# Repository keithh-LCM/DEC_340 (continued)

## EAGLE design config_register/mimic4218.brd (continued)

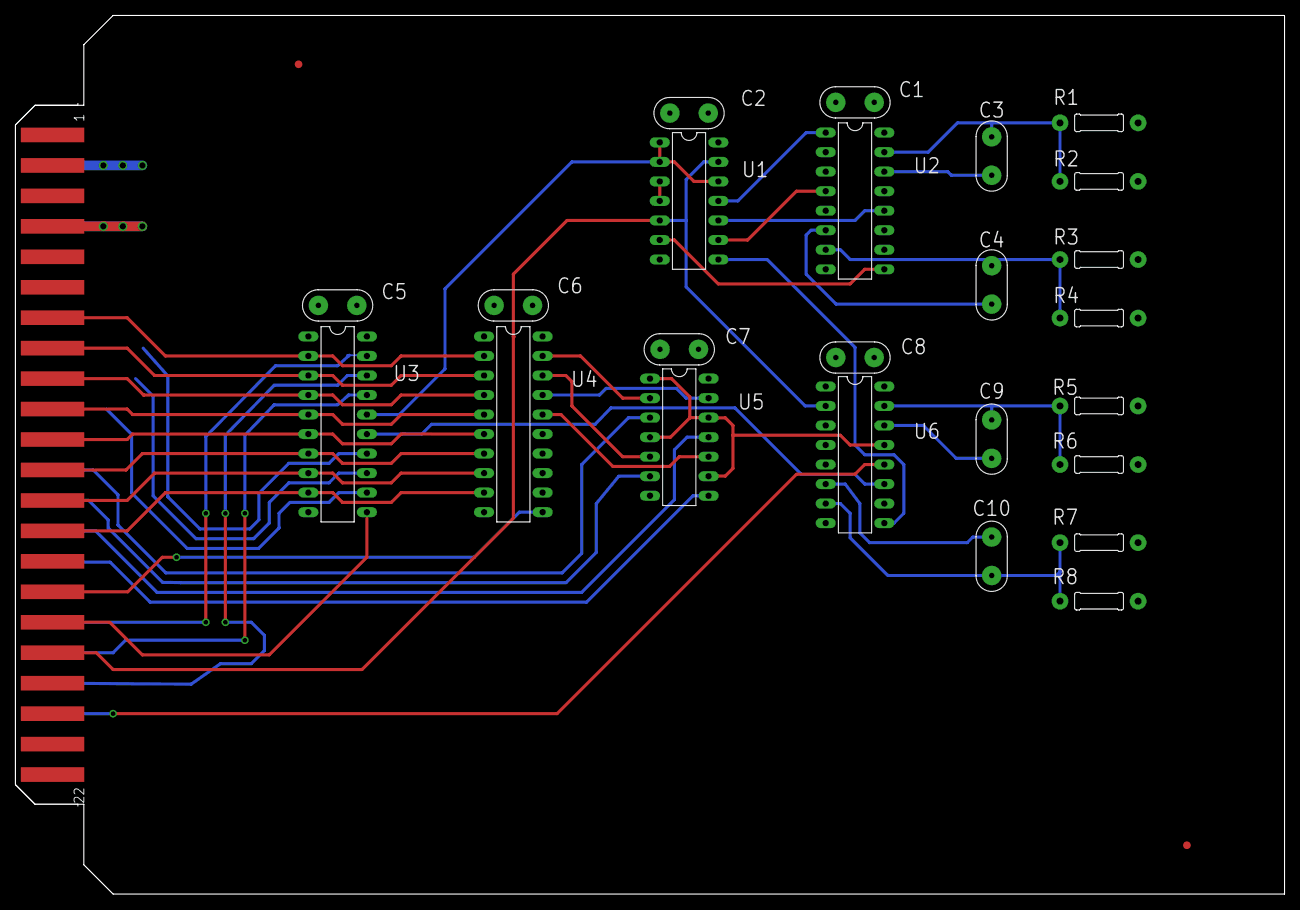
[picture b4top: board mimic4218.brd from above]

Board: 4 copper layers, 165.1 x 114.3 mm, 27 parts (0 on the bottom side), 42 nets.

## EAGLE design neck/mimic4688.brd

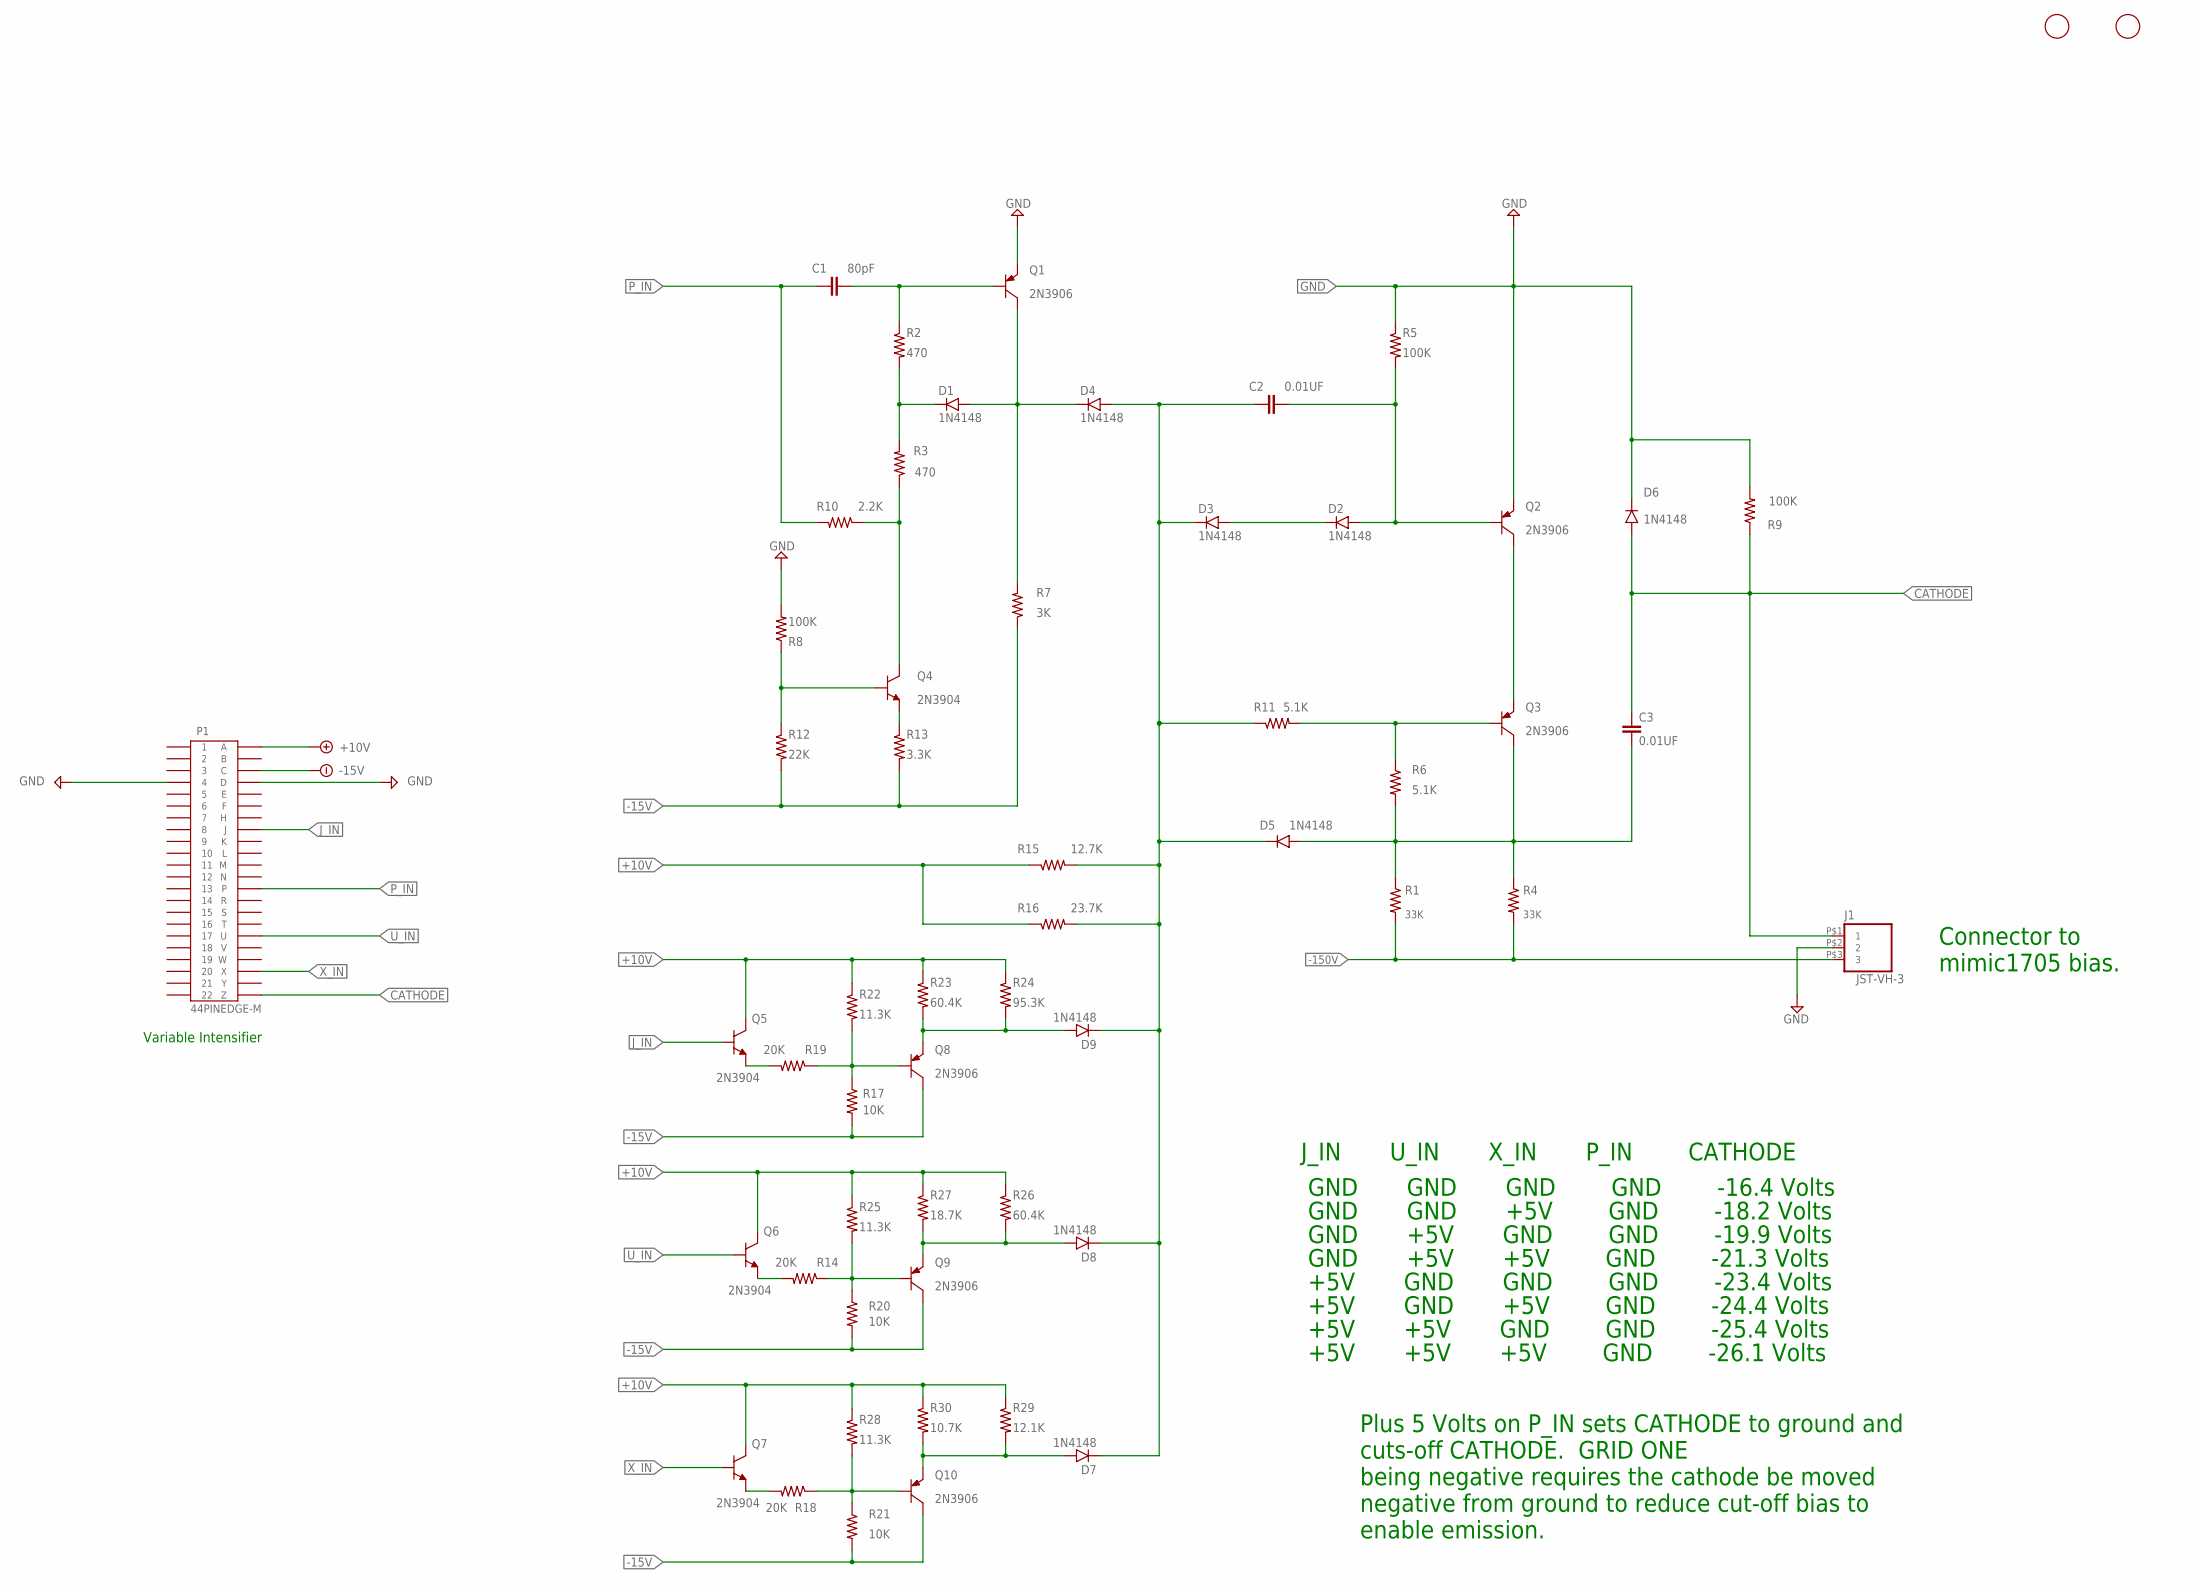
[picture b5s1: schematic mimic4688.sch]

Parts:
C1: 80pF; 5MM_TH
C2, C3: 0.01UF; 5MM_TH
D1, D2, D3, D4, D5, D6, D7, D8, D9: 1N4148; DO35-7
J1: JST-VH-3; VHR-3N
P1: 44PINEDGE-M; 44PINEDGE
Q1, Q2, Q3, Q8, Q9, Q10: 2N3906; TO92
Q4, Q5, Q6, Q7: 2N3904; TO92
R1, R4: 33K; RR02
R2, R3: 470; 0207/10
R5, R8, R9: 100K; 0207/10
R6, R11: 5.1K; 0207/10
R7: 3K; 0207/10
R10: 2.2K; 0207/10
R12: 22K; 0207/10
R13: 3.3K; 0207/10
R14, R18, R19: 20K; 0207/10
R15: 12.7K; 0207/10
R16: 23.7K; 0207/10
R17, R20, R21: 10K; 0207/10
R22, R25, R28: 11.3K; 0207/10
R23, R26: 60.4K; 0207/10
R24: 95.3K; 0207/10
R27: 18.7K; 0207/10
R29: 12.1K; 0207/10
R30: 10.7K; 0207/10
U$1, U$2: FIDUCIAL; FIDUCIAL_1MM

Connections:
+10V: P1.A, Q5.3 (C), Q6.3 (C), Q7.3 (C), R15.1, R16.1, R22.1, R23.1, R24.1, R25.1, R26.1, R27.1, R28.1, R29.1, R30.1
-15V: P1.C, Q8.1 (C), Q9.1 (C), Q10.1 (C), R7.1, R12.2, R13.2, R17.2, R20.2, R21.2
-150V: J1.P$3 (3), R1.2, R4.2
CATHODE: C3.1, D6.A, J1.P$1 (1), P1.Z, R9.1
GND: D6.C, J1.P$2 (2), P1.4, P1.D, Q1.3 (E), Q2.3 (E), R5.1, R8.2, R9.2
J_IN: P1.J, Q5.2 (B)
unnamed: C1.2, Q1.2 (B), R2.1
unnamed: Q9.2 (B), R14.1, R20.1, R25.2
unnamed: D8.A, Q9.3 (E), R26.2, R27.2
unnamed: Q7.1 (E), R18.2
unnamed: Q10.2 (B), R18.1, R21.1, R28.2
unnamed: Q6.1 (E), R14.2
unnamed: D1.A, D4.C, Q1.1 (C), R7.2
unnamed: D1.C, R2.2, R3.2
unnamed: Q4.3 (C), R3.1, R10.1
unnamed: Q5.1 (E), R19.2
unnamed: Q4.1 (E), R13.1
unnamed: Q4.2 (B), R8.1, R12.1
unnamed: Q8.2 (B), R17.1, R19.1, R22.2
unnamed: D2.C, D3.A
unnamed: Q2.1 (C), Q3.3 (E)
unnamed: D9.A, Q8.3 (E), R23.2, R24.2
unnamed: D7.A, Q10.3 (E), R29.2, R30.2
unnamed: Q3.2 (B), R6.1, R11.2
unnamed: C2.2, D2.A, Q2.2 (B), R5.2
unnamed: C2.1, D3.C, D4.A, D5.C, D7.C, D8.C, D9.C, R11.1, R15.2, R16.2
P_IN: C1.1, P1.P, R10.2
U_IN: P1.U, Q6.2 (B)
X_IN: P1.X, Q7.2 (B)
Y_OUT: C3.2, D5.A, Q3.1 (C), R1.1, R4.1, R6.2

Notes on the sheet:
Plus 5 Volts on P_IN sets CATHODE to ground and cuts-off CATHODE. GRID ONE being negative requires the cathode be moved negative from ground to reduce cut-off bias to enable emission.
J_IN U_IN X_IN P_IN CATHODE
GND GND GND GND -16.4 Volts
GND GND +5V GND -18.2 Volts
GND +5V GND GND -19.9 Volts
GND +5V +5V GND -21.3 Volts
+5V GND GND GND -23.4 Volts
+5V GND +5V GND -24.4 Volts
+5V +5V GND GND -25.4 Volts
+5V +5V +5V GND -26.1 Volts
Connector to mimic1705 bias.
Variable Intensifier

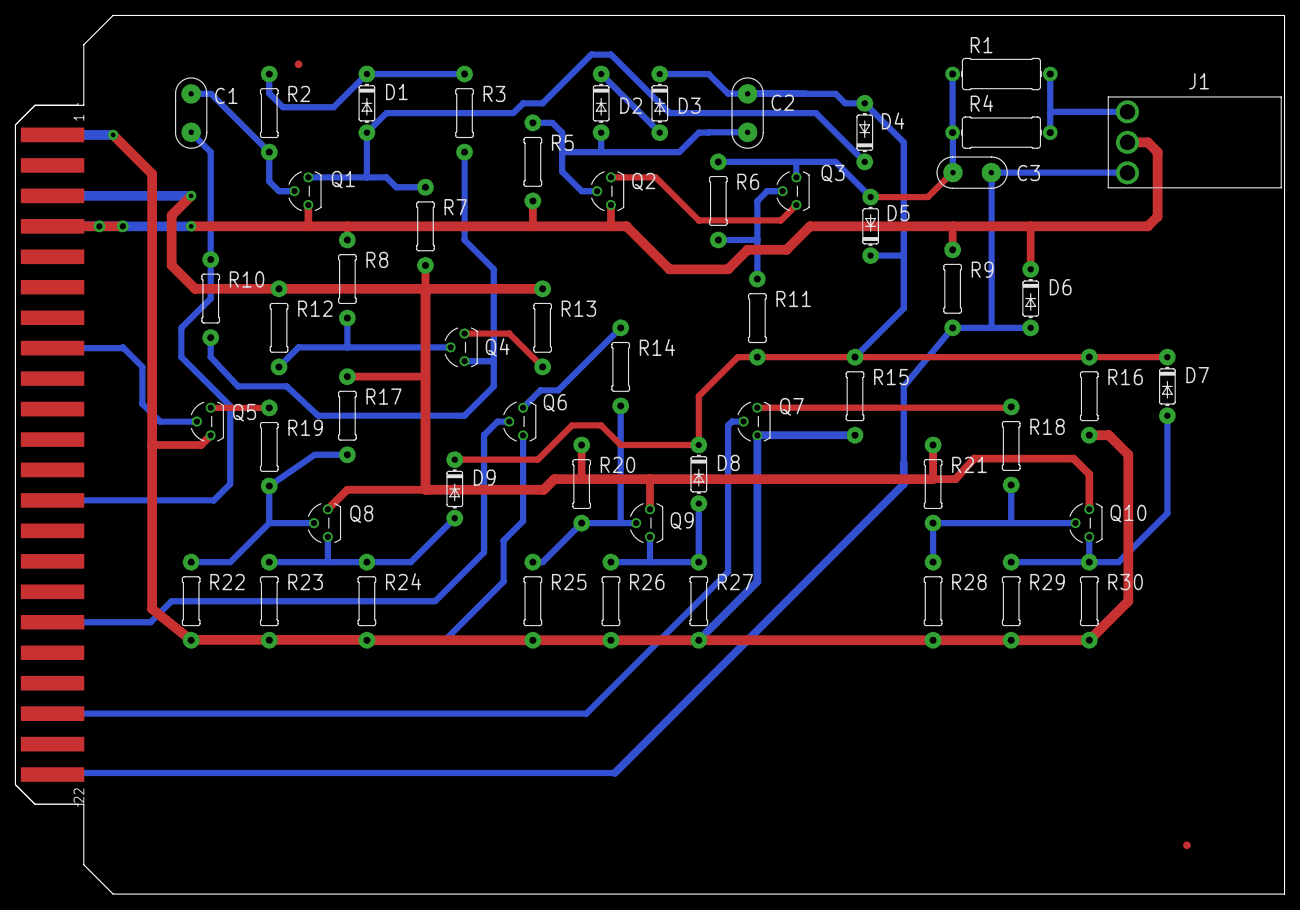
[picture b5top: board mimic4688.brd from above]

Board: 2 copper layers, 165.1 x 114.3 mm, 56 parts (0 on the bottom side), 30 nets.

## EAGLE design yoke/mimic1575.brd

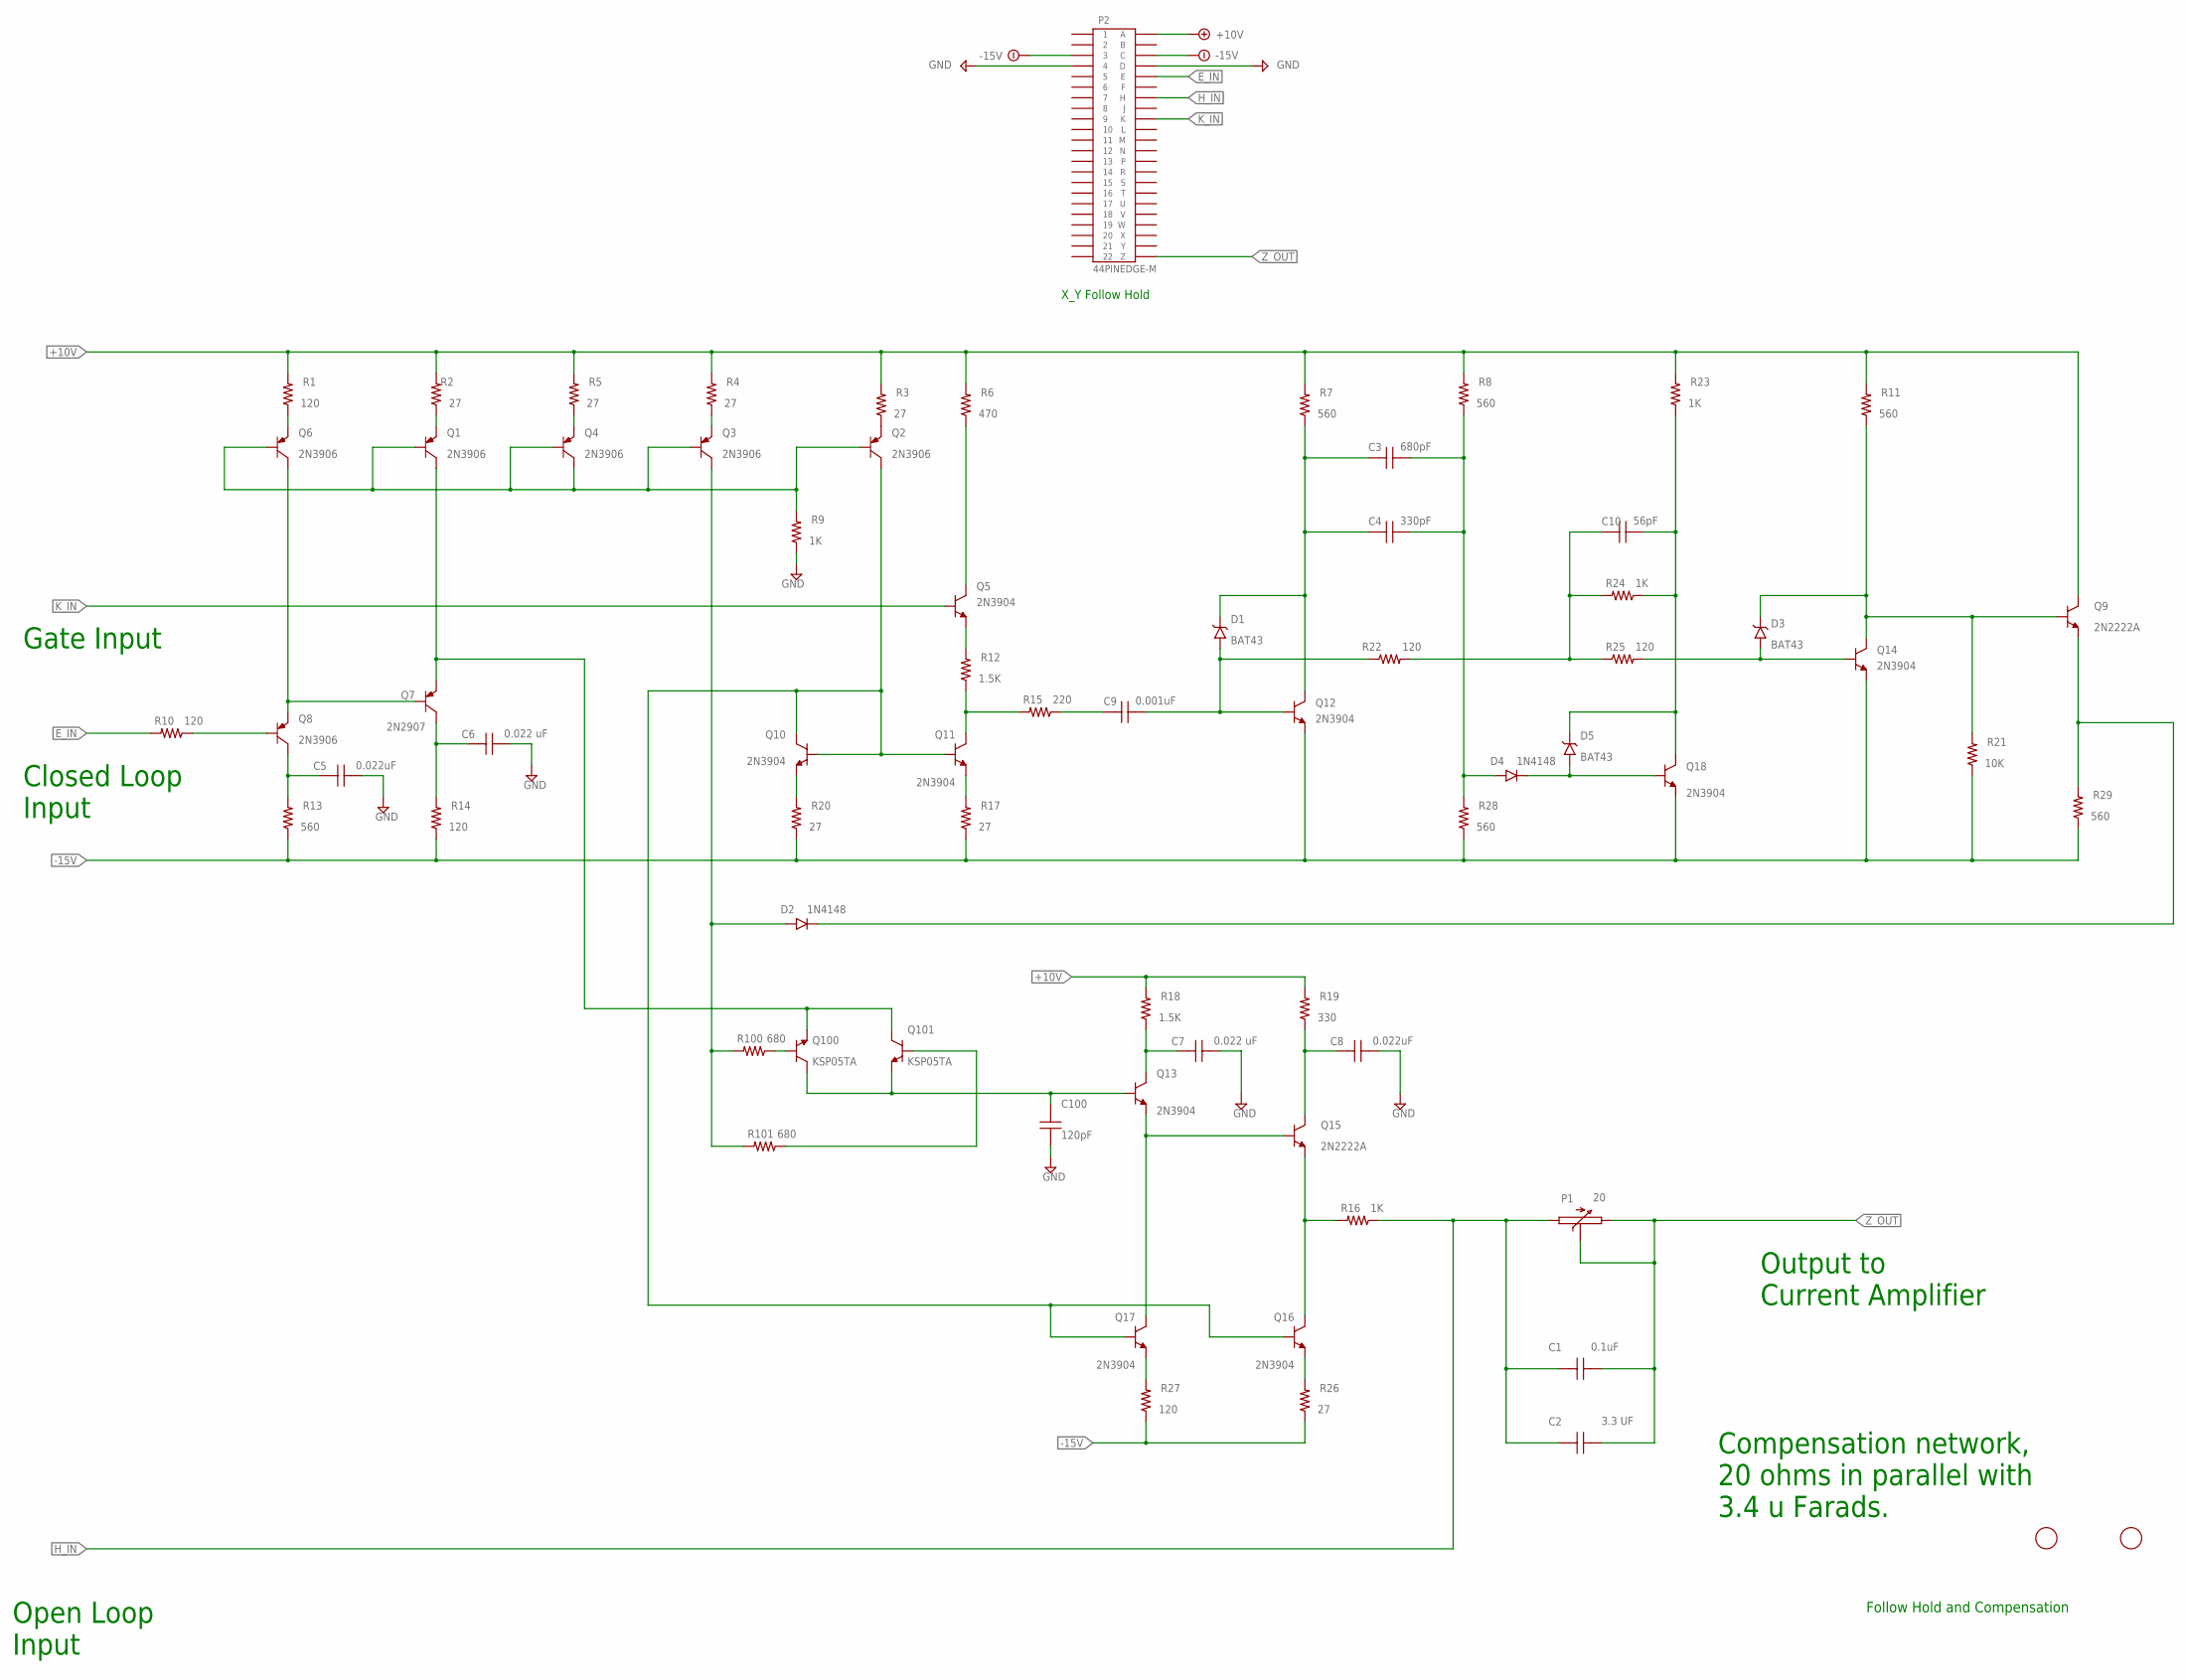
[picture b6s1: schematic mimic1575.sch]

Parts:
C1: 0.1uF; 5MM_TH
C2: 3.3 UF; ECW-FD2W335K
C3: 680pF; 5MM_TH; MPN 1000 pf
C4: 330pF; 5MM_TH; MPN 1000 pf
C5, C8: 0.022uF; CAP-ZERO-PT-ZERO-22UF-250V-FILM
C6, C7: 0.022 uF; CAP-ZERO-PT-ZERO-22UF-250V-FILM
C9: 0.001uF; 5MM_TH; MPN 1000 pf
C10: 56pF; 5MM_TH; MPN 68 pF
C100: 120pF; 5MM_TH; MPN 1000 pf
D1, D3, D5: BAT43; DO35-7
D2, D4: 1N4148; DO35-7
P1: 20; 3006P
P2: 44PINEDGE-M; 44PINEDGE
Q1, Q2, Q3, Q4, Q6, Q8: 2N3906; TO92
Q5, Q10, Q11, Q12, Q13, Q14, Q16, Q17, Q18: 2N3904; TO92
Q7: 2N2907; TO18
Q9, Q15: 2N2222A; TO18
Q100, Q101: KSP05TA; TO92
R1, R10, R14, R22, R25, R27: 120; R_QUARTERWATT
R2, R3, R4, R5, R17, R20, R26: 27; R_QUARTERWATT
R6: 470; R_QUARTERWATT
R7, R8, R11, R13, R28, R29: 560; R_QUARTERWATT
R9, R16, R23, R24: 1K; R_QUARTERWATT
R12, R18: 1.5K; R_QUARTERWATT
R15: 220; R_QUARTERWATT
R19: 330; R_QUARTERWATT
R21: 10K; R_QUARTERWATT
R100, R101: 680; R_QUARTERWATT
U$1, U$2: FIDUCIAL; FIDUCIAL_1MM

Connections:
+10V: P2.A, Q9.3 (C), R1.2, R2.2, R3.2, R4.2, R5.2, R6.2, R7.2, R8.2, R11.2, R18.2, R19.2, R23.2
-15V: P2.3, P2.C, Q12.1 (E), Q14.1 (E), Q18.1 (E), R13.1, R14.1, R17.1, R20.1, R21.1, R26.1, R27.1, R28.1, R29.1
E_IN: P2.E, R10.2
GND: C5.1, C6.1, C7.1, C8.1, C100.2, P2.4, P2.D, R9.1
H_IN: C1.1, C2.1, P1.1, P2.H, R16.1
K_IN: P2.K, Q5.2 (B)
unnamed: C9.1, R15.1
unnamed: C3.1, C4.1, D1.C, Q12.3 (C), R7.1
unnamed: C9.2, D1.A, Q12.2 (B), R22.1
unnamed: C10.1, R22.2, R24.2, R25.1
unnamed: C10.2, D5.C, Q18.3 (C), R23.1, R24.1
unnamed: D2.C, Q9.1 (E), R29.2
unnamed: Q10.1 (E), R20.2
unnamed: D4.C, D5.A, Q18.2 (B)
unnamed: C3.2, C4.2, D4.A, R8.1, R28.2
unnamed: Q4.3 (E), R5.1
unnamed: D3.C, Q9.2 (B), Q14.3 (C), R11.1, R21.2
unnamed: D3.A, Q14.2 (B), R25.2
unnamed: C6.2, Q7.3 (C), R14.2
unnamed: Q2.1 (C), Q10.2 (B), Q10.3 (C), Q11.2 (B), Q16.2 (B), Q17.2 (B)
unnamed: Q1.1 (C), Q7.1 (E), Q100.1 (E), Q101.3 (C)
unnamed: Q3.3 (E), R4.1
unnamed: Q100.2 (B), R100.1
unnamed: Q17.1 (E), R27.2
unnamed: Q101.2 (B), R101.1
unnamed: C100.1, Q13.2 (B), Q100.3 (C), Q101.1 (E)
unnamed: Q1.2 (B), Q2.2 (B), Q3.2 (B), Q4.1 (C), Q4.2 (B), Q6.2 (B), R9.2
unnamed: Q13.1 (E), Q15.2 (B), Q17.3 (C)
unnamed: D2.A, Q3.1 (C), R100.2, R101.2
unnamed: Q2.3 (E), R3.1
unnamed: Q8.2 (B), R10.1
unnamed: Q6.3 (E), R1.1
unnamed: C7.2, Q13.3 (C), R18.1
unnamed: Q11.1 (E), R17.2
unnamed: Q6.1 (C), Q7.2 (B), Q8.3 (E)
unnamed: C5.2, Q8.1 (C), R13.2
unnamed: Q1.3 (E), R2.1
unnamed: Q11.3 (C), R12.1, R15.2
unnamed: Q16.1 (E), R26.2
unnamed: Q5.1 (E), R12.2
unnamed: Q5.3 (C), R6.1
unnamed: Q15.1 (E), Q16.3 (C), R16.2
unnamed: C8.2, Q15.3 (C), R19.1
Z_OUT: C1.2, C2.2, P1.2, P1.3, P2.Z

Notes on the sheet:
Follow Hold and Compensation
Compensation network, 20 ohms in parallel with 3.4 u Farads.
Open Loop Input
Closed Loop Input
Gate Input
Output to Current Amplifier
X_Y Follow Hold

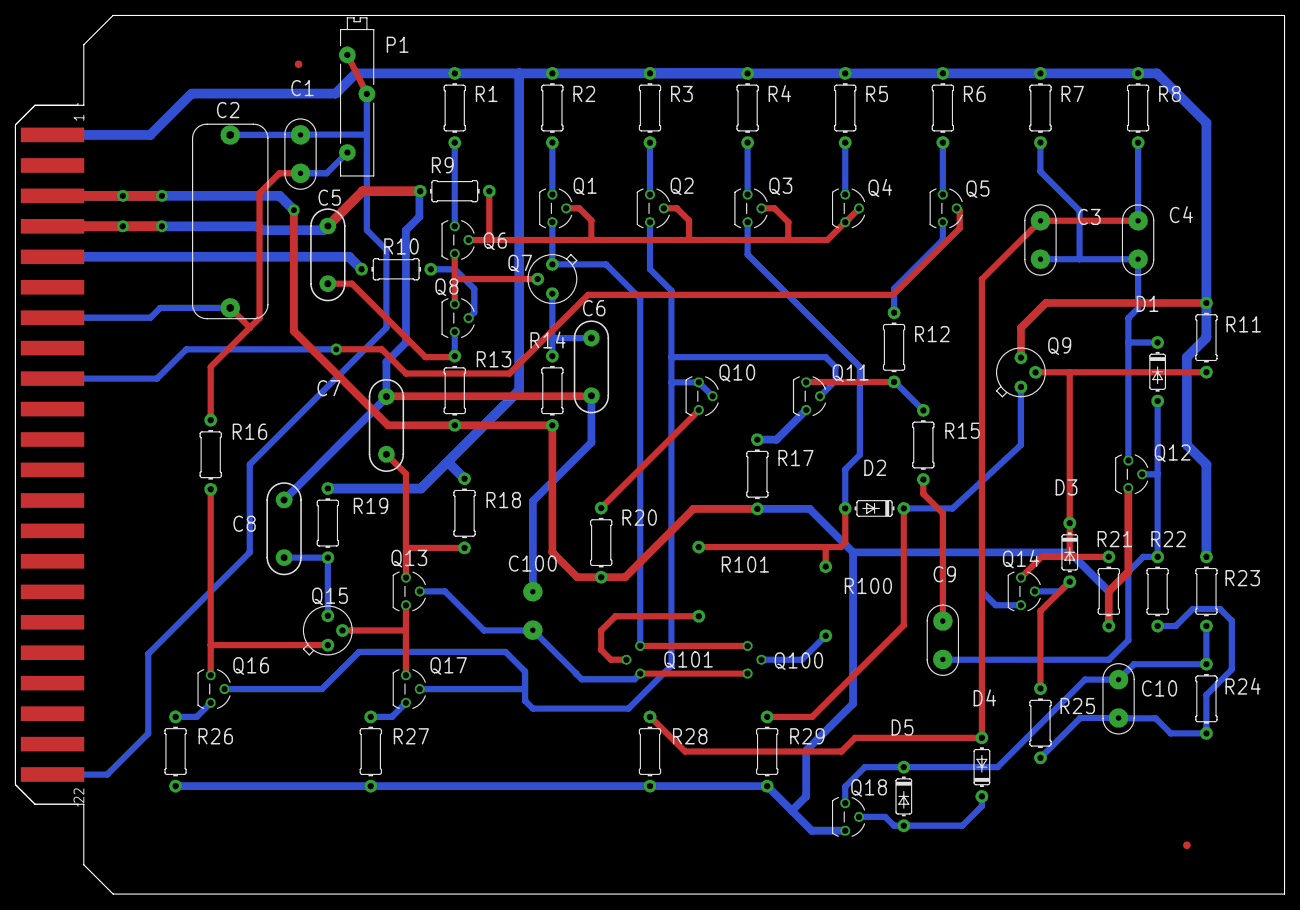
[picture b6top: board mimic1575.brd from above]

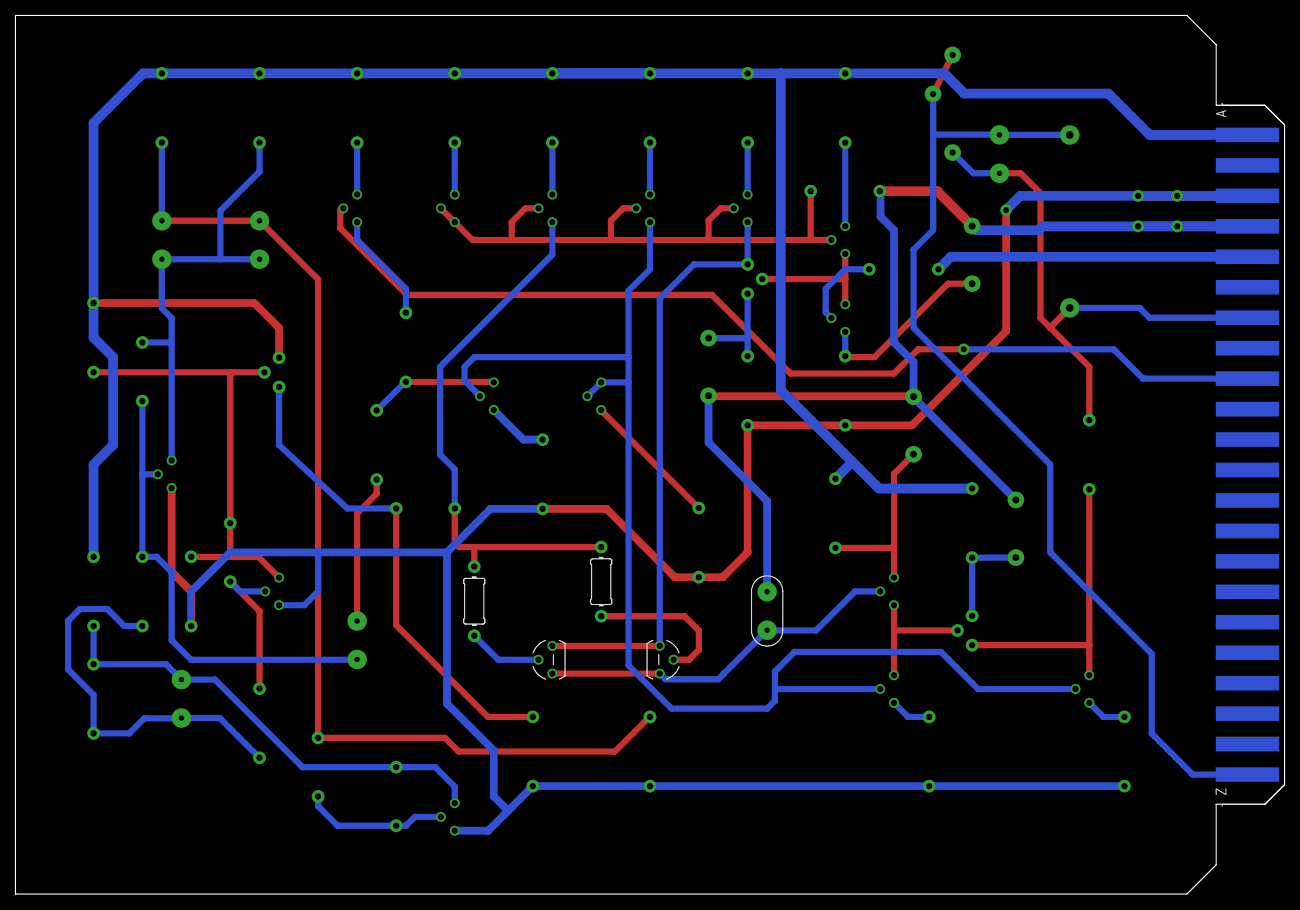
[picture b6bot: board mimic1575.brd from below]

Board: 2 copper layers, 165.1 x 114.3 mm, 71 parts (5 on the bottom side), 44 nets.

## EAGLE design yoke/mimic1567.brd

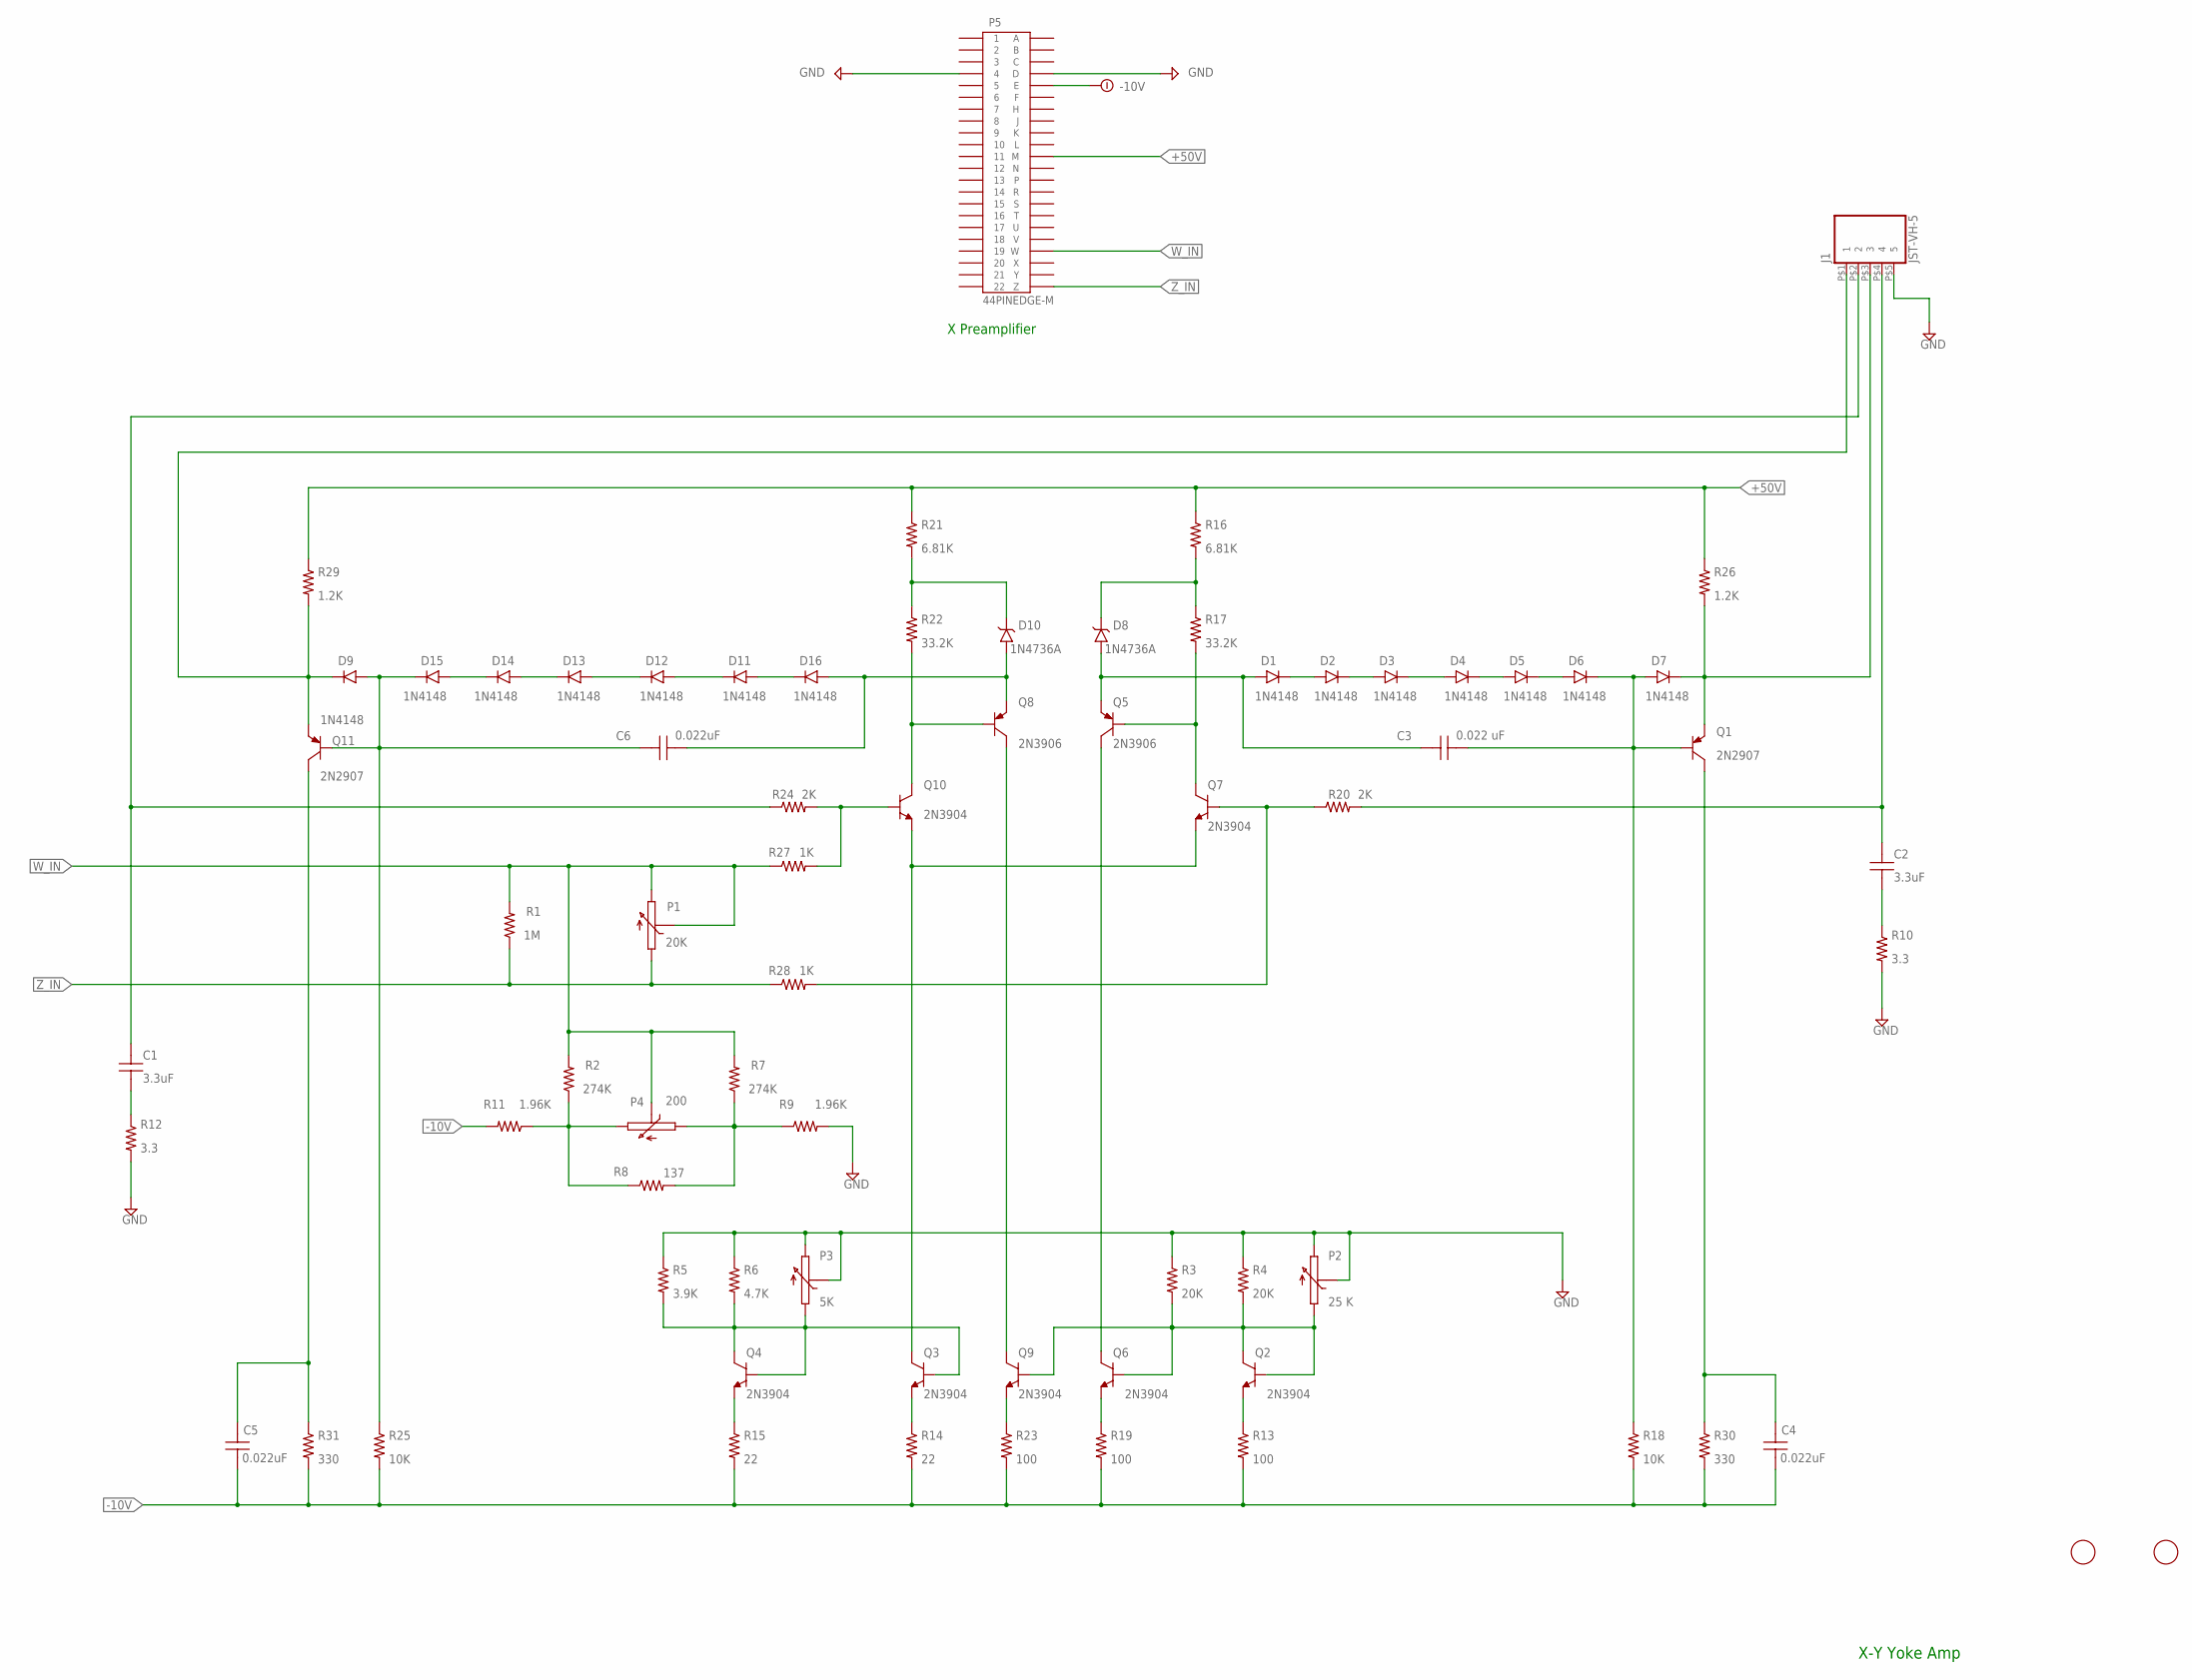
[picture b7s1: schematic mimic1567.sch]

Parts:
C1, C2: 3.3uF; CAP-3-PT-ZERO-3UF-250V-FILM
C3: 0.022 uF; CAP-ZERO-PT-ZERO-22UF-250V-FILM
C4, C5, C6: 0.022uF; CAP-ZERO-PT-ZERO-22UF-250V-FILM
D1, D2, D3, D4, D5, D6, D7, D9, D11, D12, D13, D14, D15, D16: 1N4148; DO35-7
D8, D10: 1N4736A; DO41
J1: JST-VH-5; VHR-5N
P1: 20K; 3006P
P2: 25 K; 3006P
P3: 5K; 3006P
P4: 200; 3006P
P5: 44PINEDGE-M; 44PINEDGE
Q1, Q11: 2N2907; TO18
Q2, Q3, Q4, Q6, Q7, Q9, Q10: 2N3904; TO92
Q5, Q8: 2N3906; TO92
R1: 1M; R_QUARTERWATT
R2, R7: 274K; R_QUARTERWATT
R3, R4: 20K; R_QUARTERWATT
R5: 3.9K; R_QUARTERWATT
R6: 4.7K; R_QUARTERWATT
R8: 137; R_QUARTERWATT
R9, R11: 1.96K; R_QUARTERWATT
R10, R12: 3.3; 0309/12
R13, R19, R23: 100; R_QUARTERWATT
R14, R15: 22; R_QUARTERWATT
R16, R21: 6.81K; R_HALFWATT
R17, R22: 33.2K; R_HALFWATT
R18, R25: 10K; R_HALFWATT
R20, R24: 2K; R_QUARTERWATT
R26, R29: 1.2K; R_FIVEWATT
R27, R28: 1K; R_QUARTERWATT
R30, R31: 330; R_ONEWATT
U$1, U$2: FIDUCIAL; FIDUCIAL_1MM

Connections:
+50V: P5.M, R16.1, R21.1, R26.1, R29.1
-10V: C4.1, C5.1, P5.E, R11.2, R13.2, R14.2, R15.2, R18.2, R19.2, R23.2, R25.2, R30.2, R31.2
GND: J1.P$5 (5), P2.2, P2.3, P3.2, P3.3, P5.4, P5.D, R3.1, R4.1, R5.1, R6.1, R9.2, R10.2, R12.2
unnamed: Q4.1 (E), R15.1
unnamed: C2.1, J1.P$4 (4), R20.2
unnamed: C2.2, R10.1
unnamed: P2.1, Q2.2 (B), Q2.3 (C), Q6.2 (B), Q9.2 (B), R3.2, R4.2
unnamed: D7.C, J1.P$3 (3), Q1.1 (E), R26.2
unnamed: Q7.2 (B), R20.1, R28.2
unnamed: C3.2, D6.C, D7.A, Q1.2 (B), R18.1
unnamed: C4.2, Q1.3 (C), R30.1
unnamed: Q8.1 (C), Q9.3 (C)
unnamed: D5.C, D6.A
unnamed: D4.C, D5.A
unnamed: D3.C, D4.A
unnamed: D2.C, D3.A
unnamed: D1.C, D2.A
unnamed: C3.1, D1.A, D8.A, Q5.3 (E)
unnamed: Q5.2 (B), Q7.3 (C), R17.2
unnamed: D8.C, R16.2, R17.1
unnamed: Q3.1 (E), R14.1
unnamed: Q3.3 (C), Q7.1 (E), Q10.1 (E)
unnamed: D10.C, R21.2, R22.1
unnamed: Q5.1 (C), Q6.3 (C)
unnamed: P4.1, R7.1, R8.2, R9.1
unnamed: Q9.1 (E), R23.1
unnamed: Q6.1 (E), R19.1
unnamed: Q8.2 (B), Q10.3 (C), R22.2
unnamed: Q2.1 (E), R13.1
unnamed: C1.1, J1.P$2 (2), R24.1
unnamed: P3.1, Q3.2 (B), Q4.2 (B), Q4.3 (C), R5.2, R6.2
unnamed: C1.2, R12.1
unnamed: D9.C, J1.P$1 (1), Q11.1 (E), R29.2
unnamed: C6.1, D9.A, D15.C, Q11.2 (B), R25.1
unnamed: C5.2, Q11.3 (C), R31.1
unnamed: D14.C, D15.A
unnamed: D13.C, D14.A
unnamed: D12.C, D13.A
unnamed: D11.C, D12.A
unnamed: D11.A, D16.C
unnamed: C6.2, D10.A, D16.A, Q8.3 (E)
unnamed: Q10.2 (B), R24.2, R27.2
unnamed: P4.3, R2.1, R8.1, R11.1
W_IN: P1.2, P1.3, P4.2, P5.W, R1.2, R2.2, R7.2, R27.1
Z_IN: P1.1, P5.Z, R1.1, R28.1

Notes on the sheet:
X-Y Yoke Amp
X Preamplifier

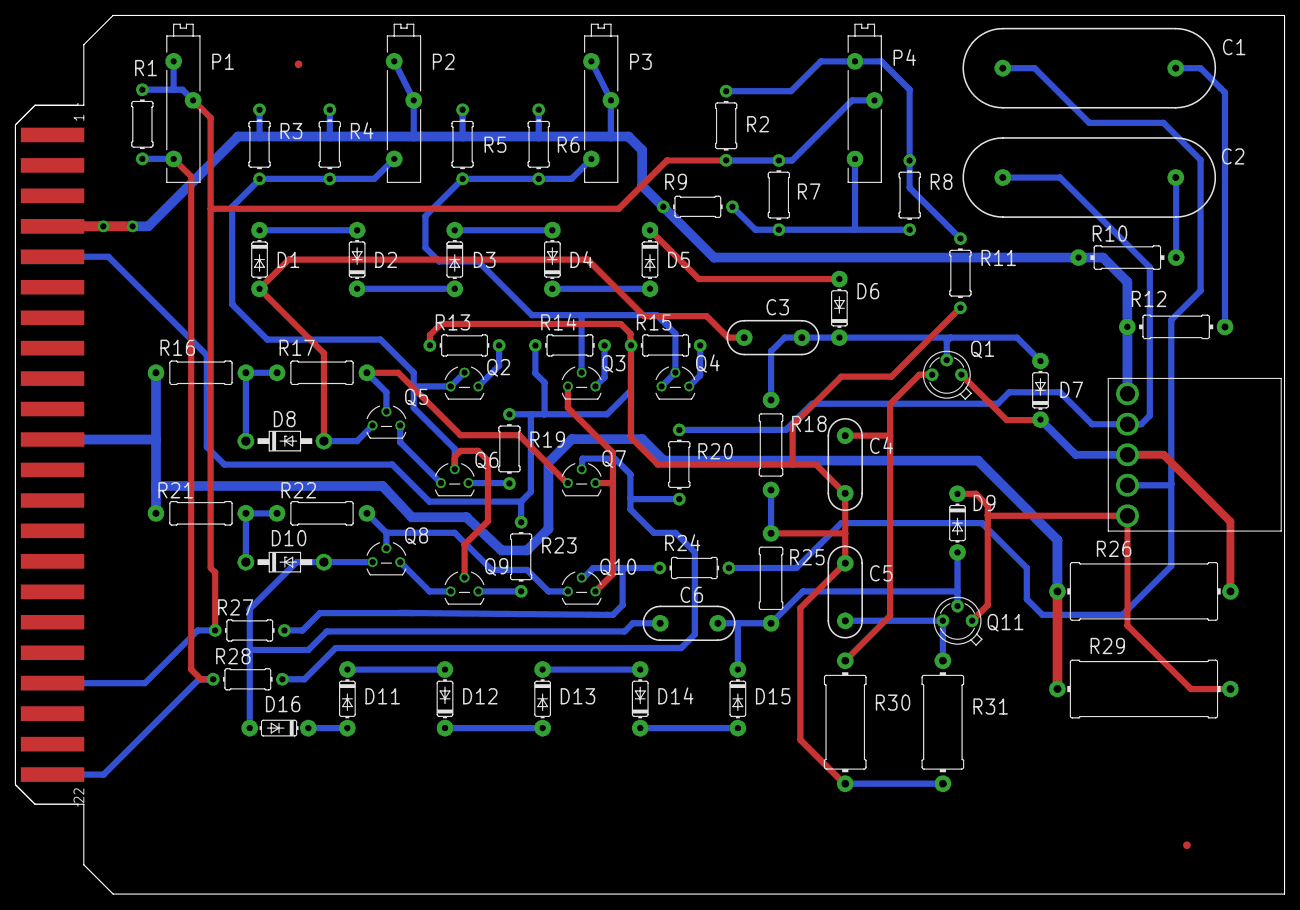
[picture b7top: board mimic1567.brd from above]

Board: 2 copper layers, 165.1 x 114.3 mm, 72 parts (0 on the bottom side), 45 nets.
